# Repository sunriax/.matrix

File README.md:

# . Matrix Display Controller

The MDC (Matrix Display Controller) is to interact with a dot matrix display (like the [Kingbright TA20](https://at.rs-online.com/web/p/led-displays/4516650?sra=pmpn)) over `SPI` bus or `UART` (See the command list below).

# Board

| Download | Description |
|-------|:------:|
| [Schematic](https://cadlab.io/project/25253/main/circuit/UENCL21hdHJpeC5raWNhZF9zY2g%3D) | Complete Schematic of the Display|
| [KiCAD](https://cadlab.io/project/25253/main/circuit/UENCL21hdHJpeC5raWNhZF9wY2I%3D) | KiCAD files |
| [Gerber](https://cadlab.io/project/25253/main/circuit/UENCL21hdHJpeC5raWNhZF9wY2I%3D) | Gerber production and drill files |

## 3D Model

| TOP | BOT |
|-----|-----|
|  |  | 

## Agenda

| Board | Status |
|-------|:------:|
| [Schematic](https://cadlab.io/project/25253/main/circuit/UENCL21hdHJpeC5raWNhZF9zY2g%3D) | ✔️ Done |
| [Board](https://cadlab.io/project/25253/main/circuit/UENCL21hdHJpeC5raWNhZF9wY2I%3D) | ✔️ Done |
| [Partlist](./PCB/docs/matrix.csv) | ✔️ Done |
| Production | ✔️ Done |
| [Assembly](pcb.png) | ✔️ Done |
| Case | ❌ Open |

# Firmware 

| Image                      | Download |
|----------------------------|----------|
| Display | [zip](https://github.com/sunriax/.matrix/releases/latest/download/matrix-firmware.zip) / [tar.gz](https://github.com/sunriax/.matrix/releases/latest/download/matrix-firmware.tar.gz) |
| Demo (ATmega16) | [zip](https://github.com/sunriax/.matrix/releases/latest/download/test-firmware-atmega16a.zip) / [tar.gz](https://github.com/sunriax/.matrix/releases/latest/download/test-firmware-atmega16a.tar.gz) |

# Display

The display can be driven in two modes either the standard (`spi`) mode or the `uart` mode.

## SPI mode

The display can be controlled with the `matrix` library. The library can be found in the [TEST project](./Firmware/TEST/main.c). The library is modular and can be adapted onto other plattforms. For platform adaptions the `spi` library has to be rewritten for the target platform. Currently the library can be used with an `ATmega16A`.

### Startup

``` c
// User libraries
#include "matrix/matrix.h"

// ...
int main(void)
{
	matrix_init();
	_delay_ms(1000);
	matrix_clear_all();
	_delay_ms(1000);
}
```

### Standard commands

| Command                       | Description                                    |
|-------------------------------|------------------------------------------------|
| `matrix_init()`               | Initializes the display                        |
| `matrix_buffer(0-255, ARRAY)` | Send an array (5*7) bits to a specific display |
| `matrix_buffer_all(ARRAY)`    | Send an array (5*7) bits to all displays       |
| `matrix_char(0-255, ASCII)`   | Send an ASCII char to a specific display       |
| `matrix_string(STRING)`       | Send an ASCII string to a all display          |
| `matrix_clear(0-255)`         | Clear a specific display                       |
| `matrix_clear_all()`          | Clear all displays                             |

### Speical commands

| Define                 | VALUE   | Description                |
|------------------------|---------|----------------------------|
| `MATRIX_EEPROM_CHAR0`  | `0x00`  | EEPROM address of MEMORY 0 |
| `MATRIX_EEPROM_CHAR0`  | `0x01`  | EEPROM address of MEMORY 1 |
| ...                    | ...     | ...                        |
| `MATRIX_EEPROM_CHAR0`  | `0x0E`  | EEPROM address of MEMORY E |
| `MATRIX_EEPROM_CHAR0`  | `0x0F`  | EEPROM address of MEMORY F |

| Command                                   | Description                                    |
|-------------------------------------------|------------------------------------------------|
| `matrix_prom_write(0-255, DEFINE, ARRAY)` | Save an array (5*7) to the display EEPROM      |
| `matrix_prom_read(0-255, DEFINE)`         | Load an array from EEPROM to the display       |

### Example

``` c
// TEST Connection
//
//          uC                 DISPLAY 0              DISPLAY 1
//  ~~~~~~~~~~~~~~~~~+    +~~~~~~~~~~~~~~~~~+    +~~~~~~~~~~~~~~~~~+
//    A  (M)         |    |                 |    |                 |
//    T  (E)     VCC +----+ VCC         VCC +----+ VCC         VCC |
//    M  (G)         |    |                 |    |                 |
//    E  (A)    MOSI +----+ MOSI       MISO +----+ MOSI       MISO |
//    G  (C)     SCK +----+ SCK         SCK +----+ SCK         SCK |
//    A  (A)      SS +----+ SS           SS +----+ SS           SS |
//    1  (R)     GND +----+ GND         GND +----+ GND         GND |
//    6  (D)         |    |                 |    |                 |
//    A              |    +~~~~~~~~~~~~~~~~~+    +~~~~~~~~~~~~~~~~~+
//  ~~~~~~~~~~~~~~~~~+

#define F_CPU 12000000UL    // System clock (required for delay)

// System libraries
#include <avr/io.h>
#include <util/delay.h>

// User libraries
#include "matrix/matrix.h"

// ...
int main(void)
{
	matrix_init();
	_delay_ms(1000);
	matrix_clear_all();
	_delay_ms(1000);

    unsigned char buffer[] = {
		0b01000,
		0b01000,
		0b01000,
		0b01000,
		0b01000,
		0b01000,
		0b11111
	}; 

    // Send buffer to display 0
    matrix_buffer(0, buffer);
	_delay_ms(1000);

    // Send buffer to all displays
    matrix_buffer_all(buffer);
	_delay_ms(1000);

    // Send ASCII char to display 0
    matrix_char(0, 'A');
	_delay_ms(1000);

    // Send string to displays
    matrix_string(0, "TEST");
	_delay_ms(1000);

    // Clear display 0
    matrix_clear(0);
	_delay_ms(1000);

    // Clear all displays
    matrix_clear_all();
	_delay_ms(1000);

    // !!! Only one time necessary !!!
    // !!!!!!!!!!!!!!!!!!!!!!!!!!!!!!!!!!!!!!!!!!!!!!!!!!!
    // !!! Warning:                                    !!!
    // !!! Don´t call this function in a while(1) loop !!!
    // !!! This will damage the EEPROM                 !!!
    // !!!!!!!!!!!!!!!!!!!!!!!!!!!!!!!!!!!!!!!!!!!!!!!!!!!

    // Save buffer in display EEPROM
	matrix_prom_write(0, MATRIX_EEPROM_CHAR0, buffer);
	_delay_ms(1000);

    // Read data from EEPROM
    matrix_prom_read(0, MATRIX_EEPROM_CHAR0);
	_delay_ms(1000);
}
```

## UART mode

The standard ASCII characters can also be transferred to display over UART. Therefore a special configuration is necessary. Pin `SS` should be connected to ground (`GND`) before powering the display.

``` c
// TEST Connection
//
//           DISPLAY 0              USB/UART
//      +~~~~~~~~~~~~~~~~~+   +~~~~~~~~~~~~~~~~~+
//      |                 |   |                 |
//      + VCC         VCC +---+ VCC             |
//      |                 |   |             +---+
//      + MOSI       MISO +---+ TXD         | U |
//      + SCK         SCK +   |             | S |
//  +---+ SS           SS +   |             | B |
//  +---+ GND         GND +---+ GND         +---+
//      |                 |   |                 |
//      +~~~~~~~~~~~~~~~~~+   +~~~~~~~~~~~~~~~~~+
```

Characters can be sent to the display over [TeraTerm](https://osdn.net/projects/ttssh2/releases/) or [Putty](https://www.chiark.greenend.org.uk/~sgtatham/putty/latest.html)
`UART` should contain following setup:

| Parameter | Value |
|-----------|-------|
| Baudrate  | 9600  |
| Datasize  | 8 Bit |
| Parity    | None  |
| Stopbits  | 1     |

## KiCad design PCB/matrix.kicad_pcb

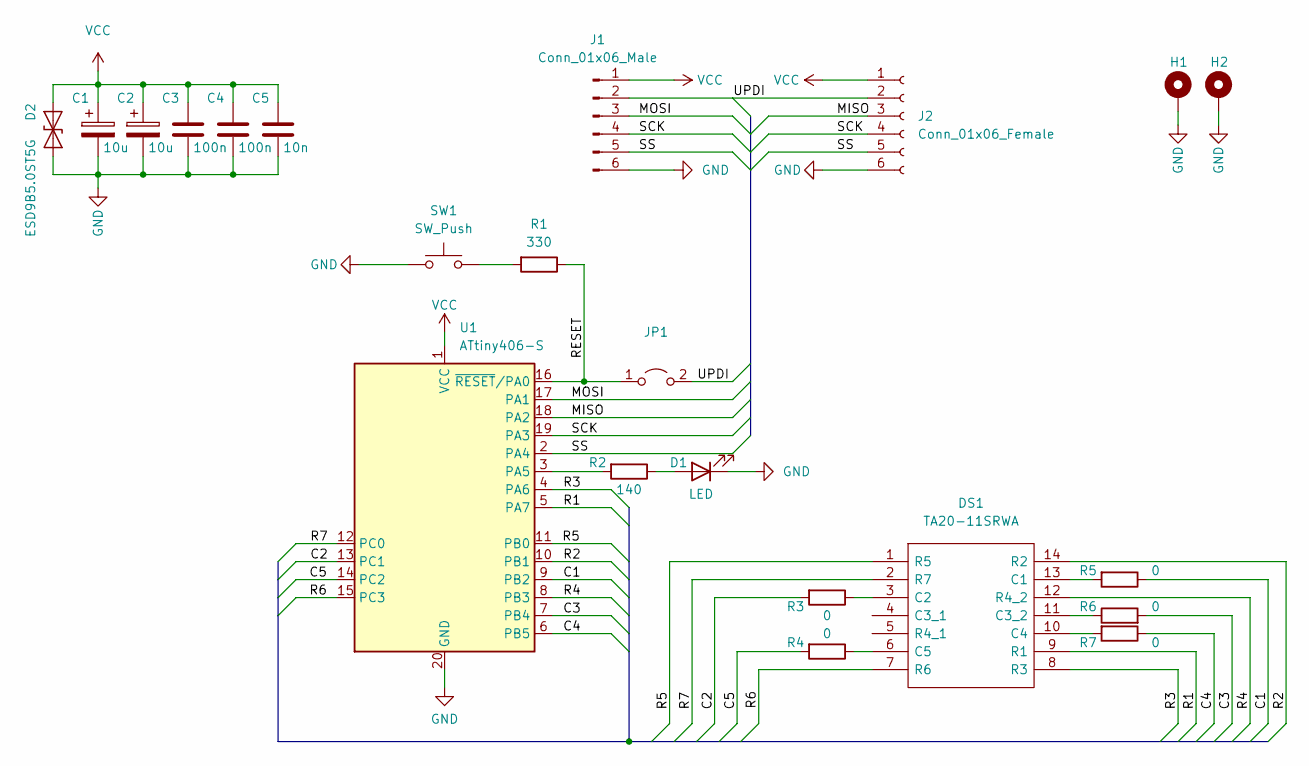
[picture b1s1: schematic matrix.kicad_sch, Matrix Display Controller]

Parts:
C1, C2: 10u; CP_Elec_4x5.8
C3, C4: 100n; C_1206_3216Metric
C5: 10n; C_1206_3216Metric
D1: LED; LED_0805_2012Metric
D2: ESD9B5.0ST5G; D_SOD-923
DS1: TA20-11SRWA; DIPS3810W50P254L3765H870Q14N; Manufacturer_Part_Number TA20-11SRWA; Mouser Part Number 604-TA20-11SRWA
H1, H2: MountingHole_3.2mm_M3_DIN965_Pad
J1: Conn_01x06_Male; PinHeader_1x06_P2.54mm_Horizontal
J2: Conn_01x06_Female; PinSocket_1x06_P2.54mm_Horizontal
JP1: PinHeader_1x02_P2.54mm_Horizontal
R1: 330; R_1206_3216Metric
R2: 140; R_1206_3216Metric
R3, R4, R5, R6, R7: 0; R_1206_3216Metric
SW1: SW_Push; SW_Push_1P1T_NO_6x6mm_H9.5mm
U1: ATtiny406-S; SOIC-20W_7.5x12.8mm_P1.27mm

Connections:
/C1: R5.1, U1.9 (PB2)
/C2: R3.2, U1.13 (PC1)
/C3: R6.2, U1.7 (PB4)
/C4: R7.1, U1.6 (PB5)
/C5: R4.2, U1.14 (PC2)
/MISO: J2.3, U1.18 (PA2)
/MOSI: J1.3, U1.17 (PA1)
/R1: DS1.9 (R1), U1.5 (PA7)
/R2: DS1.14 (R2), U1.10 (PB1)
/R3: DS1.8 (R3), U1.4 (PA6)
/R4: DS1.12 (R4_2), U1.8 (PB3)
/R5: DS1.1 (R5), U1.11 (PB0)
/R6: DS1.7 (R6), U1.15 (PC3)
/R7: DS1.2 (R7), U1.12 (PC0)
/RESET: JP1.1 (A), R1.1, U1.16 (~RESET/PA0)
/SCK: J1.4, J2.4, U1.19 (PA3)
/SS: J1.5, J2.5, U1.2 (PA4)
/UPDI: J1.2, J2.2, JP1.2 (B)
GND: C1.2, C2.2, C3.2, C4.2, C5.2, D1.1 (K), D2.1 (A1), H1.1, H2.1, J1.6, J2.6, SW1.1, U1.20 (GND)
unnamed: D1.2 (A), R2.1
unnamed: DS1.3 (C2), R3.1
unnamed: DS1.6 (C5), R4.1
unnamed: DS1.10 (C4), R7.2
unnamed: DS1.11 (C3_2), R6.1
unnamed: DS1.13 (C1), R5.2
unnamed: R1.2, SW1.2
unnamed: R2.2, U1.3 (PA5)
VCC: C1.1, C2.1, C3.1, C4.1, C5.1, D2.2 (A2), J1.1, J2.1, U1.1 (VCC)

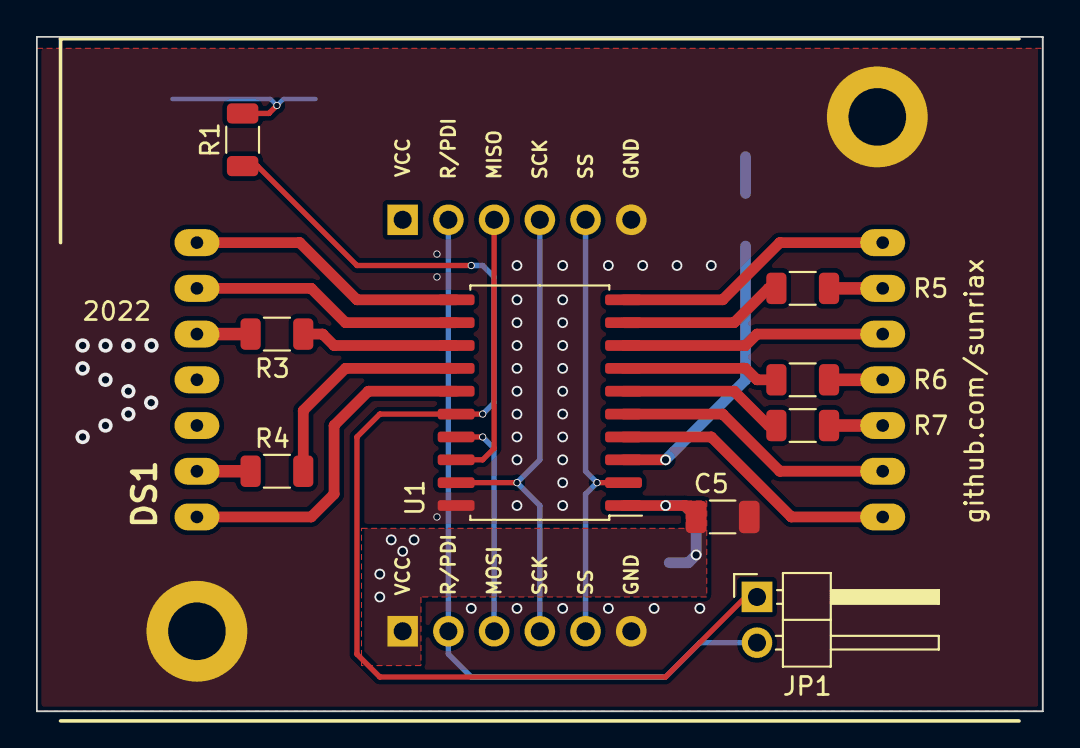
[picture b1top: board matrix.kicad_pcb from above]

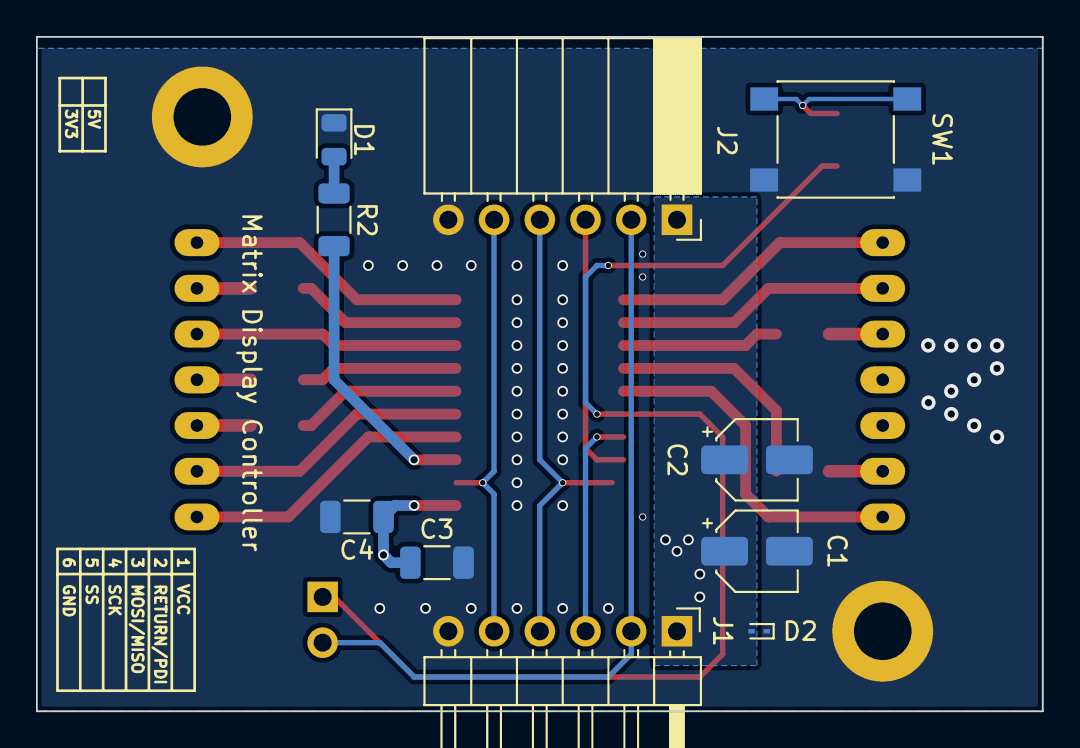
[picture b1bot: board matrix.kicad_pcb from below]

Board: 2 copper layers, 55.9 x 37.5 mm, 22 parts (10 on the bottom side), 28 nets.

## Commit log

2022-02-25 Add projects
2022-02-25 Backlink to CADLAB.io has been added.
2022-03-03 Extend firmware
2022-03-03 Change EEPROM methods
2022-03-03 Change address validation procedure
2022-03-03 Swap EEPROM display/save command
2022-03-03 Add UART mode
2022-03-04 Add TEST project
2022-03-10 Update PCB TA20 pads
2022-04-01 Code refactoring
2022-04-01 Optimized PCB
2022-04-01 Add UART support
2022-04-06 Change SPI protocol
2022-07-01 Initiate travis
2022-07-01 Fix travis
2022-07-01 Create github action
2022-07-01 Add actions
2022-07-01 Update partlist

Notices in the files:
README.md:
License: GPL v3
